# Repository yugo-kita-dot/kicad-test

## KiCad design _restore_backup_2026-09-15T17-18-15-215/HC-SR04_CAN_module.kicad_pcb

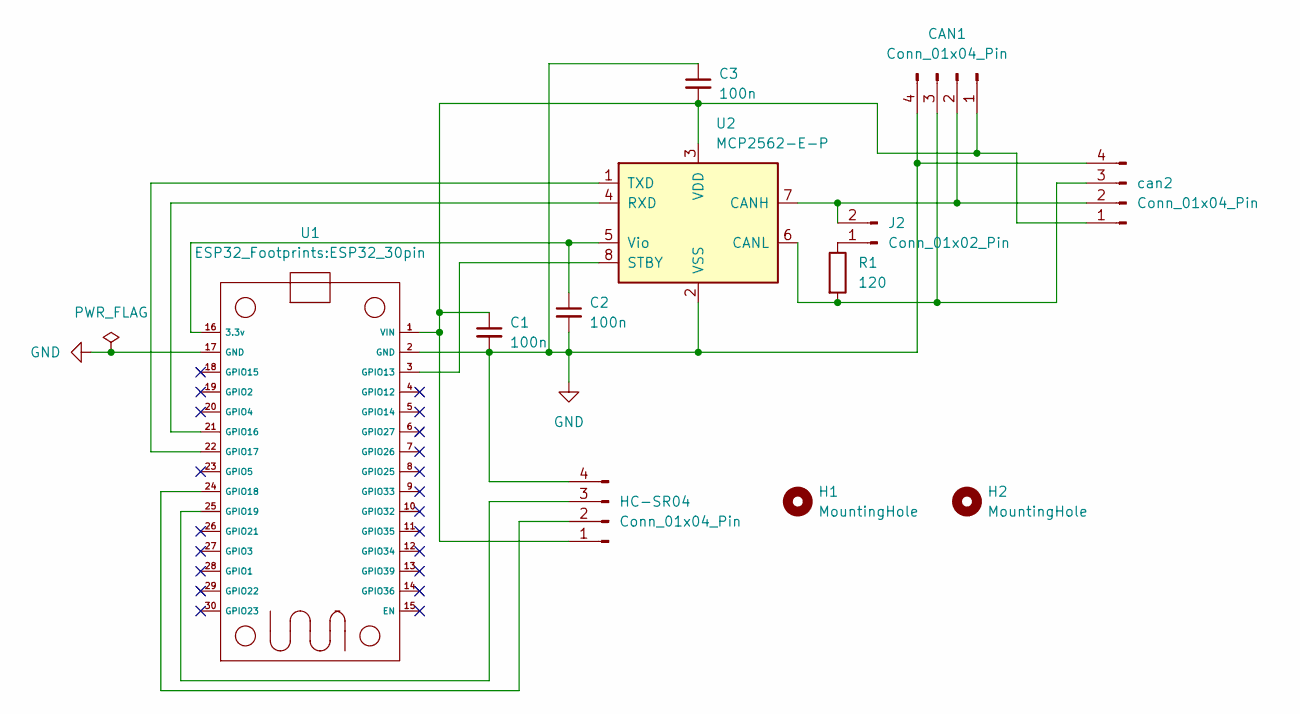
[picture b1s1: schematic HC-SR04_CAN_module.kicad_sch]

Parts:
C1, C2, C3: 100n; C_Disc_D5.0mm_W2.5mm_P2.50mm
CAN1: Conn_01x04_Pin; JST_XA_S04B-XASK-1_1x04_P2.50mm_Horizontal
H1, H2: MountingHole; MountingHole_3.2mm_M3
HC-SR04: Conn_01x04_Pin; PinHeader_1x04_P2.54mm_Vertical
J2: Conn_01x02_Pin; PinHeader_1x02_P2.54mm_Vertical
R1: 120; R_Axial_DIN0207_L6.3mm_D2.5mm_P10.16mm_Horizontal
U1: ESP32_30pin
U2: MCP2562-E-P; DIP-8_W7.62mm
can2: Conn_01x04_Pin; JST_XA_S04B-XASK-1_1x04_P2.50mm_Horizontal

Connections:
GND: C1.2, C2.2, C3.1, CAN1.4, HC-SR04.4, U1.2 (GND), U1.17 (GND), U2.2 (VSS), can2.4
unnamed: C1.1, C3.2, CAN1.1, HC-SR04.1, U1.1 (VIN), U2.3 (VDD), can2.1
unnamed: CAN1.2, J2.2, U2.7 (CANH), can2.2
unnamed: CAN1.3, R1.2, U2.6 (CANL), can2.3
unnamed: HC-SR04.2, U1.24 (GPIO18)
unnamed: HC-SR04.3, U1.25 (GPIO19)
unnamed: J2.1, R1.1
unnamed: C2.1, U1.16 (3.3v), U2.5 (Vio)
unnamed: U1.3 (GPIO13), U2.8 (STBY)
unnamed: U1.21 (GPIO16), U2.4 (RXD)
unnamed: U1.22 (GPIO17), U2.1 (TXD)

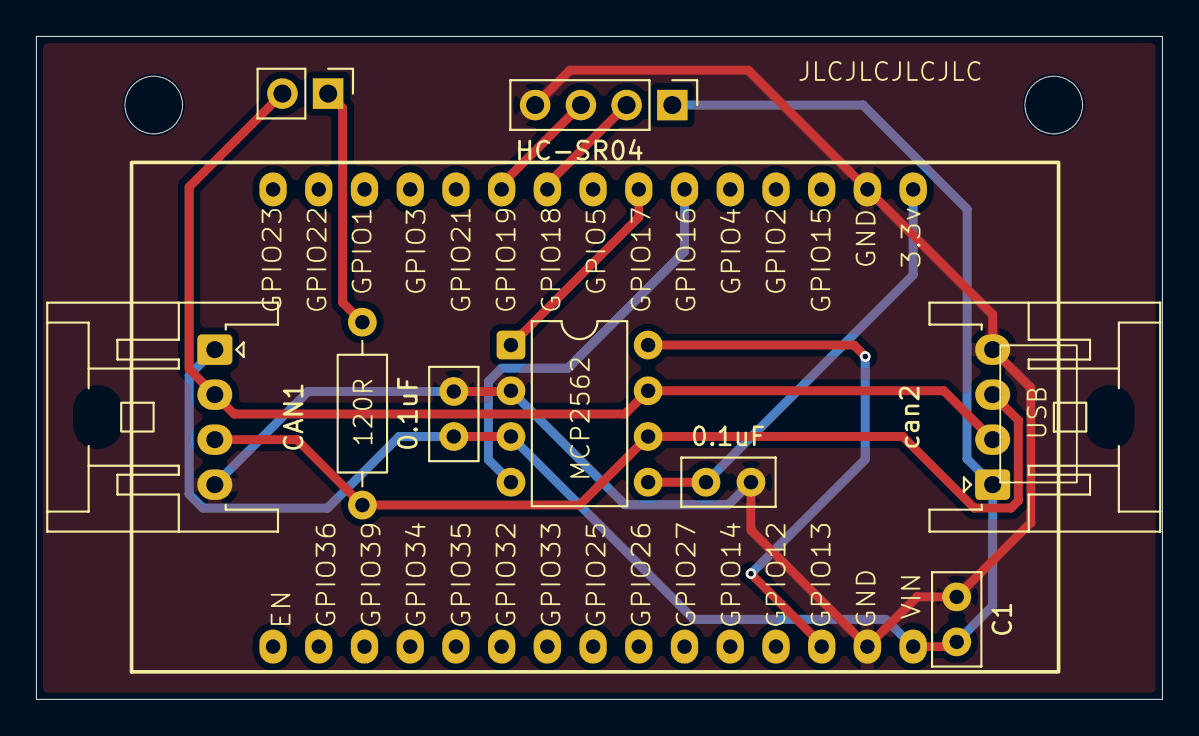
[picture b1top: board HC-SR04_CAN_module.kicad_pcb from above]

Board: 2 copper layers, 62.6 x 36.8 mm, 12 parts (0 on the bottom side), 11 nets.
